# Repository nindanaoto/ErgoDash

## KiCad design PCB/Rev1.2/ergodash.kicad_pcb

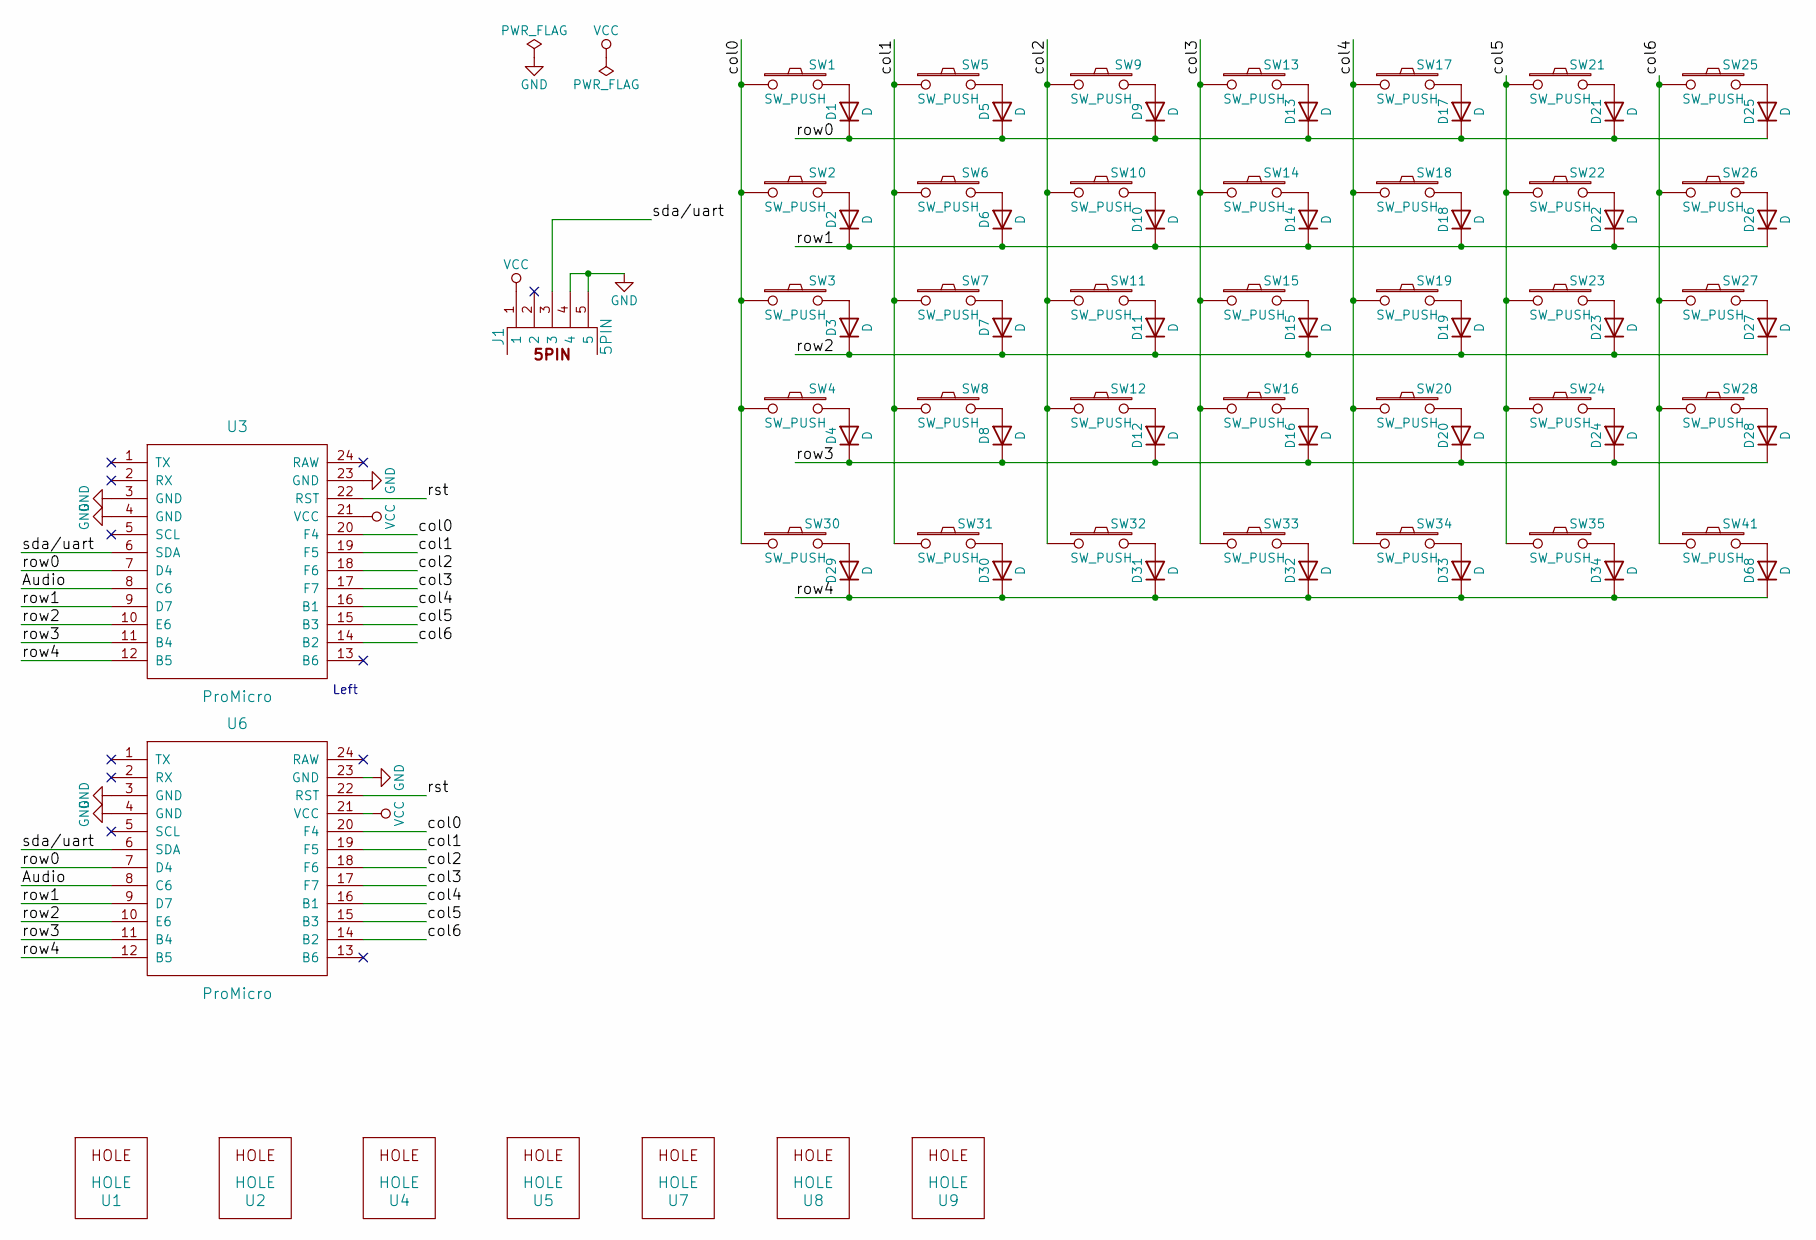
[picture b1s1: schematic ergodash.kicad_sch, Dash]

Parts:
D1, D2, D3, D4, D5, D6, D7, D8, D9, D10, D11, D12, D13, D14, D15, D16, D17, D18, D19, D20, D21, D22, D23, D24, D25, D26, D27, D28, D29, D30, D31, D32, D33, D34: D; Diode_SMD_THT3
D68: D; Diode_SMD_THT2
J1: 5PIN; trrs_jack
SW1, SW2, SW3, SW4, SW5, SW6, SW7, SW8, SW9, SW10, SW11, SW12, SW13, SW14, SW15, SW16, SW17, SW18, SW19, SW20, SW21, SW22, SW23, SW24, SW25, SW26, SW27, SW28, SW30, SW31, SW32, SW33, SW34, SW35, SW41: SW_PUSH; Kailh_socket_PG1350_optional_reversible
U1, U2, U4, U5, U7, U8, U9: HOLE; hole
U3, U6: ProMicro; ProMicro_rev

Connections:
/Audio: U3.8 (C6), U6.8 (C6)
/col0: SW1.1, SW2.1, SW3.1, SW4.1, SW30.1, U3.20 (F4), U6.20 (F4)
/col1: SW5.1, SW6.1, SW7.1, SW8.1, SW31.1, U3.19 (F5), U6.19 (F5)
/col2: SW9.1, SW10.1, SW11.1, SW12.1, SW32.1, U3.18 (F6), U6.18 (F6)
/col3: SW13.1, SW14.1, SW15.1, SW16.1, SW33.1, U3.17 (F7), U6.17 (F7)
/col4: SW17.1, SW18.1, SW19.1, SW20.1, SW34.1, U3.16 (B1), U6.16 (B1)
/col5: SW21.1, SW22.1, SW23.1, SW24.1, SW35.1, U3.15 (B3), U6.15 (B3)
/col6: SW25.1, SW26.1, SW27.1, SW28.1, SW41.1, U3.14 (B2), U6.14 (B2)
/row0: D1.1 (K), D5.1 (K), D9.1 (K), D13.1 (K), D17.1 (K), D21.1 (K), D25.1 (K), U3.7 (D4), U6.7 (D4)
/row1: D2.1 (K), D6.1 (K), D10.1 (K), D14.1 (K), D18.1 (K), D22.1 (K), D26.1 (K), U3.9 (D7), U6.9 (D7)
/row2: D3.1 (K), D7.1 (K), D11.1 (K), D15.1 (K), D19.1 (K), D23.1 (K), D27.1 (K), U3.10 (E6), U6.10 (E6)
/row3: D4.1 (K), D8.1 (K), D12.1 (K), D16.1 (K), D20.1 (K), D24.1 (K), D28.1 (K), U3.11 (B4), U6.11 (B4)
/row4: D29.1 (K), D30.1 (K), D31.1 (K), D32.1 (K), D33.1 (K), D34.1 (K), D68.1 (K), U3.12 (B5), U6.12 (B5)
/rst: U3.22 (RST), U6.22 (RST)
/sda/uart: J1.3, U3.6 (SDA), U6.6 (SDA)
/xtradata: J1.2
GND: J1.4, J1.5, U3.3 (GND), U3.4 (GND), U3.23 (GND), U6.3 (GND), U6.4 (GND), U6.23 (GND)
unnamed: D1.2 (A), SW1.2
unnamed: D2.2 (A), SW2.2
unnamed: D3.2 (A), SW3.2
unnamed: D4.2 (A), SW4.2
unnamed: D5.2 (A), SW5.2
unnamed: D6.2 (A), SW6.2
unnamed: D7.2 (A), SW7.2
unnamed: D8.2 (A), SW8.2
unnamed: D9.2 (A), SW9.2
unnamed: D10.2 (A), SW10.2
unnamed: D11.2 (A), SW11.2
unnamed: D12.2 (A), SW12.2
unnamed: D13.2 (A), SW13.2
unnamed: D14.2 (A), SW14.2
unnamed: D15.2 (A), SW15.2
unnamed: D16.2 (A), SW16.2
unnamed: D17.2 (A), SW17.2
unnamed: D18.2 (A), SW18.2
unnamed: D19.2 (A), SW19.2
unnamed: D20.2 (A), SW20.2
unnamed: D21.2 (A), SW21.2
unnamed: D22.2 (A), SW22.2
unnamed: D23.2 (A), SW23.2
unnamed: D24.2 (A), SW24.2
unnamed: D25.2 (A), SW25.2
unnamed: D26.2 (A), SW26.2
unnamed: D27.2 (A), SW27.2
unnamed: D28.2 (A), SW28.2
unnamed: D29.2 (A), SW30.2
unnamed: D30.2 (A), SW31.2
unnamed: D31.2 (A), SW32.2
unnamed: D32.2 (A), SW33.2
unnamed: D33.2 (A), SW34.2
unnamed: D34.2 (A), SW35.2
unnamed: D68.2 (A), SW41.2
VCC: J1.1, U3.21 (VCC), U6.21 (VCC)

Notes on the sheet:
Left

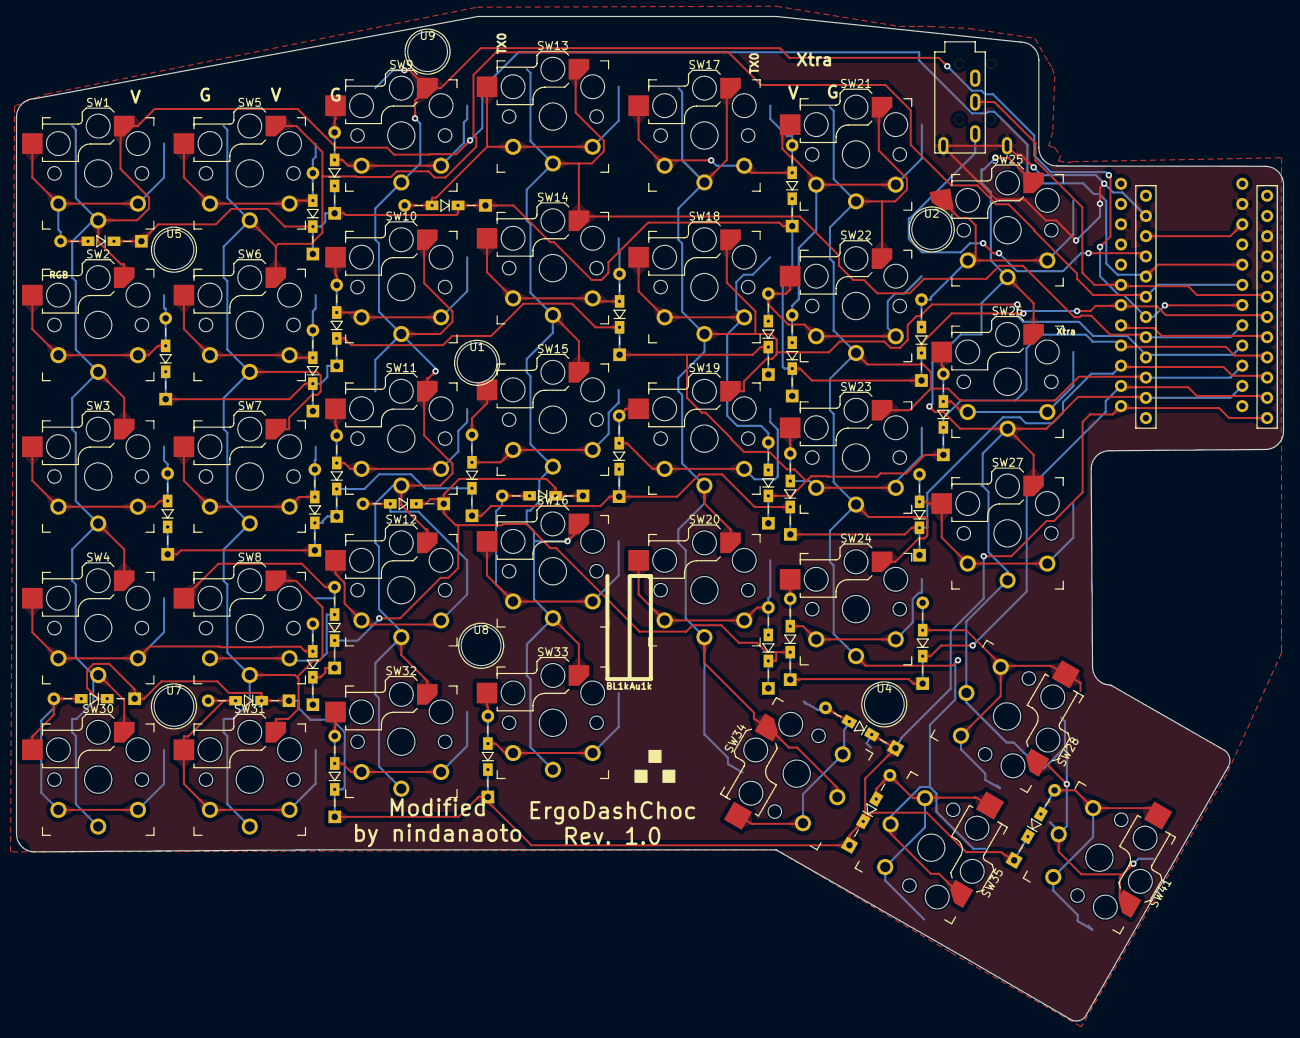
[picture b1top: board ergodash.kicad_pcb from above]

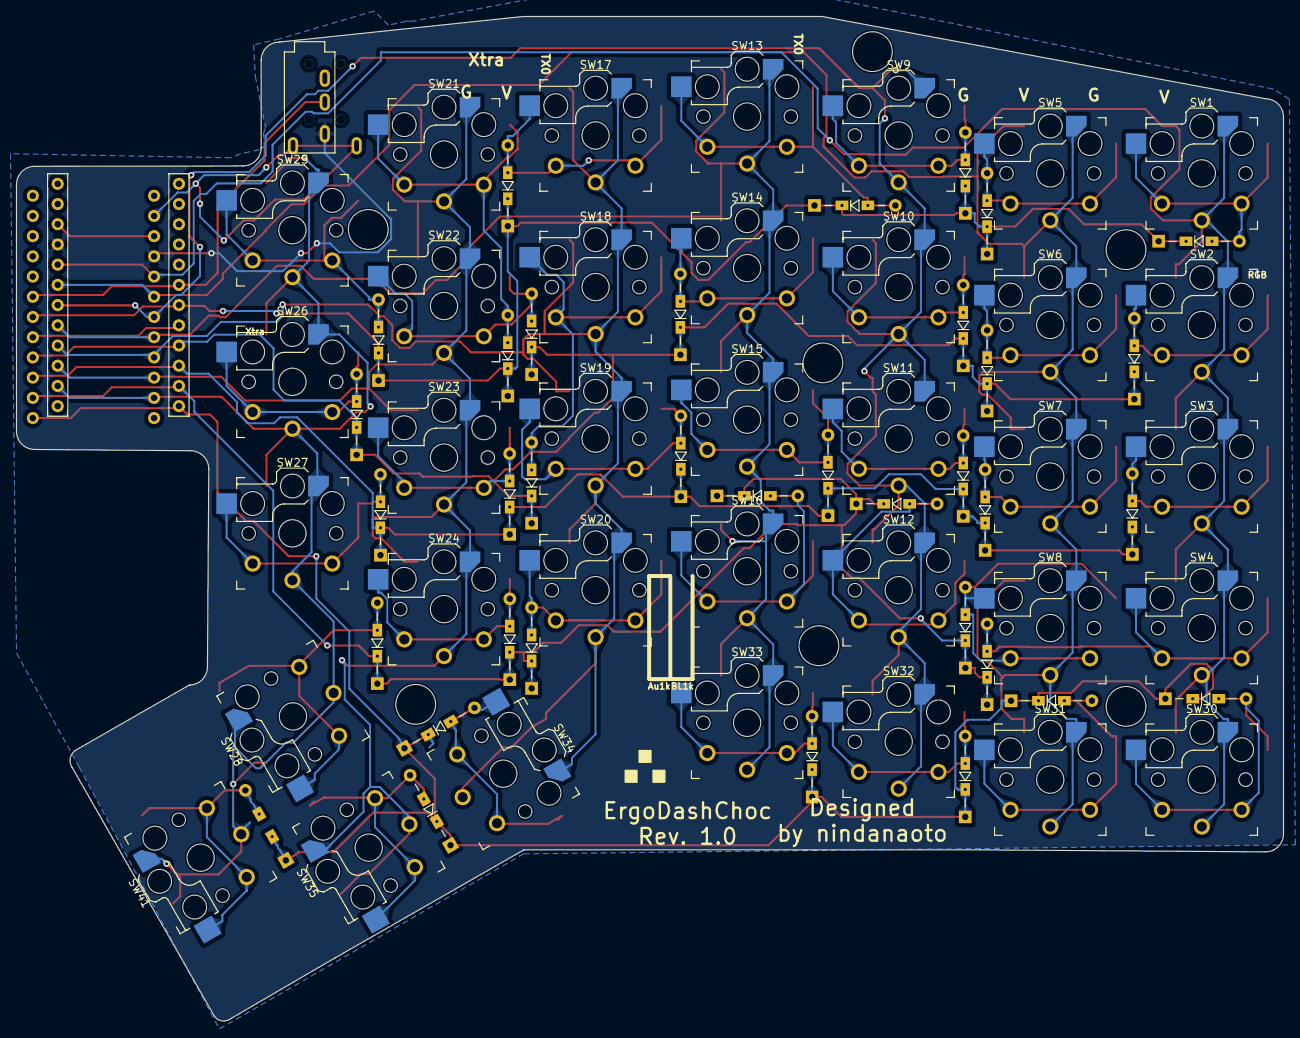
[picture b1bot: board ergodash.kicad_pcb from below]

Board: 2 copper layers, 159.2 x 126.3 mm, 80 parts (14 on the bottom side), 52 nets.

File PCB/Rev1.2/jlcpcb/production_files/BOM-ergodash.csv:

Comment,Designator,Footprint,LCSC
HOLE,U1,hole,
HOLE,U2,hole,
HOLE,U4,hole,
HOLE,U5,hole,
HOLE,U7,hole,
HOLE,U8,hole,
HOLE,U9,hole,
ProMicro,U3,ProMicro_rev,
D,D68,Diode_SMD_THT2,
SW_PUSH,SW5,Kailh_socket_PG1350_optional_reversible,
SW_PUSH,SW6,Kailh_socket_PG1350_optional_reversible,
SW_PUSH,SW7,Kailh_socket_PG1350_optional_reversible,
SW_PUSH,SW8,Kailh_socket_PG1350_optional_reversible,
SW_PUSH,SW12,Kailh_socket_PG1350_optional_reversible,
SW_PUSH,SW13,Kailh_socket_PG1350_optional_reversible,
SW_PUSH,SW14,Kailh_socket_PG1350_optional_reversible,
SW_PUSH,SW15,Kailh_socket_PG1350_optional_reversible,
SW_PUSH,SW16,Kailh_socket_PG1350_optional_reversible,
SW_PUSH,SW17,Kailh_socket_PG1350_optional_reversible,
SW_PUSH,SW18,Kailh_socket_PG1350_optional_reversible,
SW_PUSH,SW19,Kailh_socket_PG1350_optional_reversible,
SW_PUSH,SW20,Kailh_socket_PG1350_optional_reversible,
SW_PUSH,SW21,Kailh_socket_PG1350_optional_reversible,
SW_PUSH,SW25,Kailh_socket_PG1350_optional_reversible,
SW_PUSH,SW26,Kailh_socket_PG1350_optional_reversible,
SW_PUSH,SW27,Kailh_socket_PG1350_optional_reversible,
SW_PUSH,SW28,Kailh_socket_PG1350_optional_reversible,
SW_PUSH,SW31,Kailh_socket_PG1350_optional_reversible,
SW_PUSH,SW34,Kailh_socket_PG1350_optional_reversible,
SW_PUSH,SW35,Kailh_socket_PG1350_optional_reversible,
D,D1,Diode_SMD_THT3,
D,D2,Diode_SMD_THT3,
D,D3,Diode_SMD_THT3,
D,D4,Diode_SMD_THT3,
D,D5,Diode_SMD_THT3,
D,D6,Diode_SMD_THT3,
D,D7,Diode_SMD_THT3,
D,D8,Diode_SMD_THT3,
D,D9,Diode_SMD_THT3,
D,D10,Diode_SMD_THT3,
D,D11,Diode_SMD_THT3,
D,D12,Diode_SMD_THT3,
D,D13,Diode_SMD_THT3,
D,D14,Diode_SMD_THT3,
D,D16,Diode_SMD_THT3,
D,D17,Diode_SMD_THT3,
D,D19,Diode_SMD_THT3,
D,D20,Diode_SMD_THT3,
D,D21,Diode_SMD_THT3,
D,D22,Diode_SMD_THT3,
D,D23,Diode_SMD_THT3,
D,D24,Diode_SMD_THT3,
D,D25,Diode_SMD_THT3,
D,D26,Diode_SMD_THT3,
D,D27,Diode_SMD_THT3,
D,D28,Diode_SMD_THT3,
D,D29,Diode_SMD_THT3,
D,D30,Diode_SMD_THT3,
D,D31,Diode_SMD_THT3,
D,D33,Diode_SMD_THT3,
D,D32,Diode_SMD_THT3,
D,D15,Diode_SMD_THT3,
D,D18,Diode_SMD_THT3,
ProMicro,U6,ProMicro_rev,
SW_PUSH,SW1,Kailh_socket_PG1350_optional_reversible,
SW_PUSH,SW2,Kailh_socket_PG1350_optional_reversible,
SW_PUSH,SW3,Kailh_socket_PG1350_optional_reversible,
SW_PUSH,SW4,Kailh_socket_PG1350_optional_reversible,
SW_PUSH,SW9,Kailh_socket_PG1350_optional_reversible,
SW_PUSH,SW10,Kailh_socket_PG1350_optional_reversible,
SW_PUSH,SW11,Kailh_socket_PG1350_optional_reversible,
SW_PUSH,SW22,Kailh_socket_PG1350_optional_reversible,
SW_PUSH,SW23,Kailh_socket_PG1350_optional_reversible,
SW_PUSH,SW24,Kailh_socket_PG1350_optional_reversible,
SW_PUSH,SW30,Kailh_socket_PG1350_optional_reversible,
SW_PUSH,SW32,Kailh_socket_PG1350_optional_reversible,
SW_PUSH,SW33,Kailh_socket_PG1350_optional_reversible,
5PIN,J1,trrs_jack2,
SW_PUSH,SW41,Kailh_socket_PG1350_optional_reversible,
D,D34,Diode_SMD_THT3,

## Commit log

2024-07-24 choc v1 version
2024-07-24 Rev1.0
